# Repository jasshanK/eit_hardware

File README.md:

# WIP 
USE SCHEMATICS AT OWN RISK

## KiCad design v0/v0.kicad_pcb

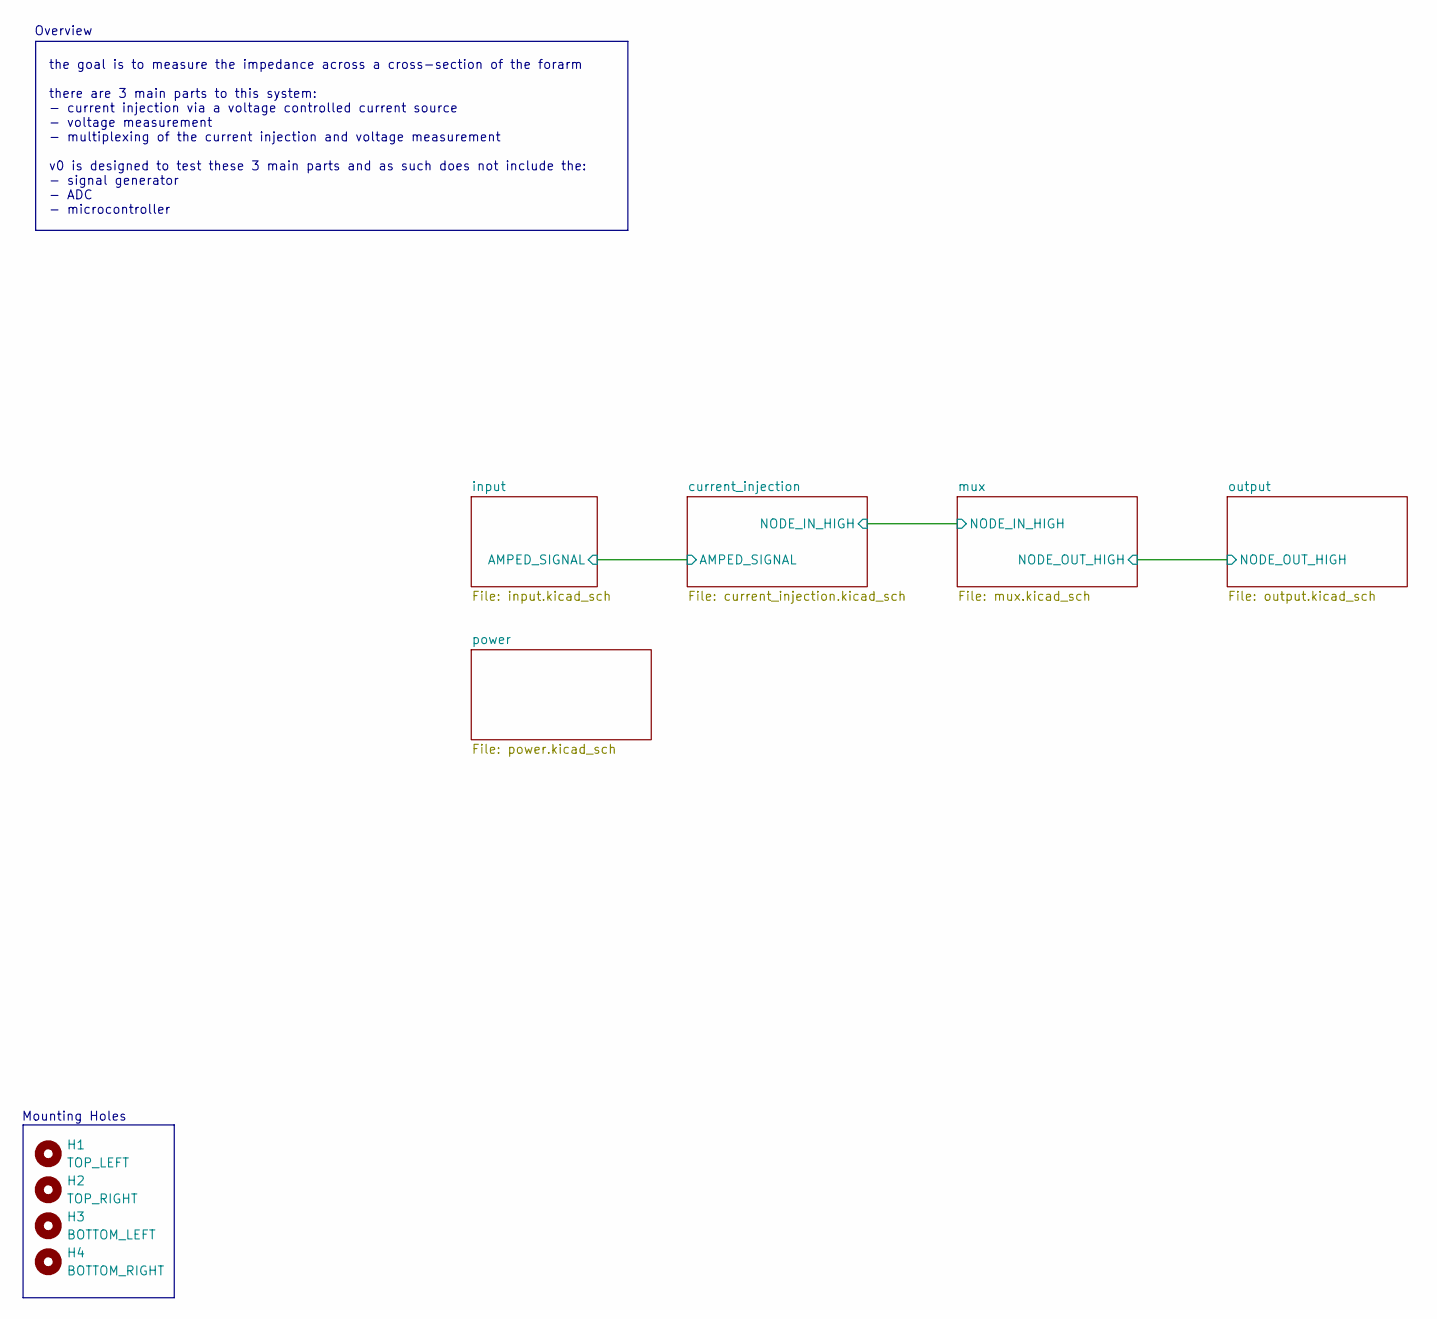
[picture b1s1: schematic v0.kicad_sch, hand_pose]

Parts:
H1: TOP_LEFT; MountingHole_2.2mm_M2
H2: TOP_RIGHT; MountingHole_2.2mm_M2
H3: BOTTOM_LEFT; MountingHole_2.2mm_M2
H4: BOTTOM_RIGHT; MountingHole_2.2mm_M2

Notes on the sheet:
the goal is to measure the impedance across a cross-section of the forarm there are 3 main parts to this system: - current injection via a voltage controlled current source - voltage measurement - multiplexing of the current injection and voltage measurement v0 is designed to test these 3 main part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
Overview
Mounting Holes

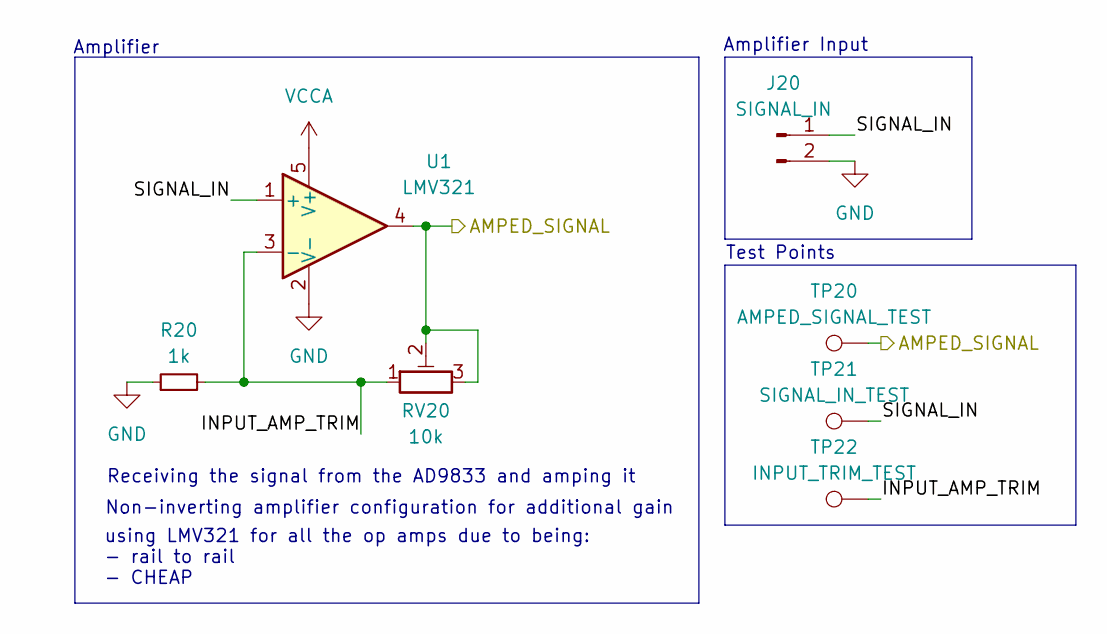
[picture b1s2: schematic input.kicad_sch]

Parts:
J20: SIGNAL_IN; PinHeader_1x02_P2.54mm_Vertical
R20: 1k; R_0402_1005Metric_Pad0.72x0.64mm_HandSolder
RV20: 10k; Potentiometer_Bourns_3296W_Vertical
TP20: AMPED_SIGNAL_TEST; TestPoint_Loop_D1.80mm_Drill1.0mm_Beaded
TP21: SIGNAL_IN_TEST; TestPoint_Loop_D1.80mm_Drill1.0mm_Beaded
TP22: INPUT_TRIM_TEST; TestPoint_Pad_1.0x1.0mm
U1: LMV321; SOT-23-5

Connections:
/current_injection/AMPED_SIGNAL: RV20.2, RV20.3, TP20.1, U1.4; also elsewhere on the board
/input/INPUT_AMP_TRIM: R20.2, RV20.1, TP22.1, U1.3 (-)
/input/SIGNAL_IN: J20.1, TP21.1, U1.1 (+)
GND: J20.2, R20.1, U1.2 (V-); also elsewhere on the board
VCCA: U1.5 (V+); also elsewhere on the board

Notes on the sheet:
Receiving the signal from the AD9833 and amping it
using LMV321 for all the op amps due to being: - rail to rail - CHEAP
Amplifier Input
Test Points
Non-inverting amplifier configuration for additional gain
Amplifier

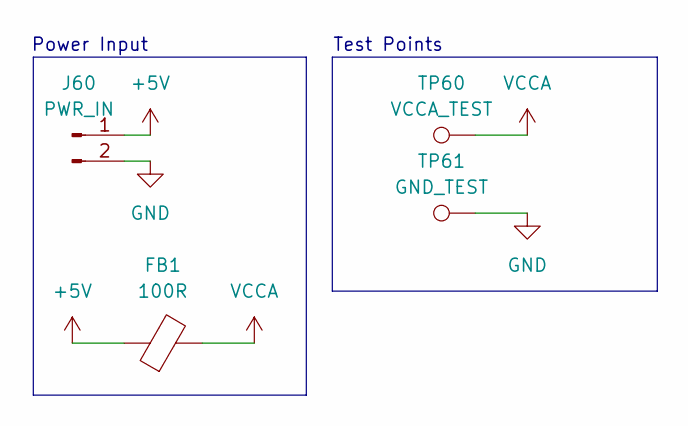
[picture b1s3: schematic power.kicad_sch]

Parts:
FB1: 100R; L_0805_2012Metric_Pad1.05x1.20mm_HandSolder
J60: PWR_IN; PinHeader_1x02_P2.54mm_Vertical
TP60: VCCA_TEST; TestPoint_Loop_D1.80mm_Drill1.0mm_Beaded
TP61: GND_TEST; TestPoint_Loop_D1.80mm_Drill1.0mm_Beaded

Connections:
+5V: FB1.1, J60.1
GND: J60.2, TP61.1; also elsewhere on the board
VCCA: FB1.2, TP60.1; also elsewhere on the board

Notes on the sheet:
Test Points
Power Input

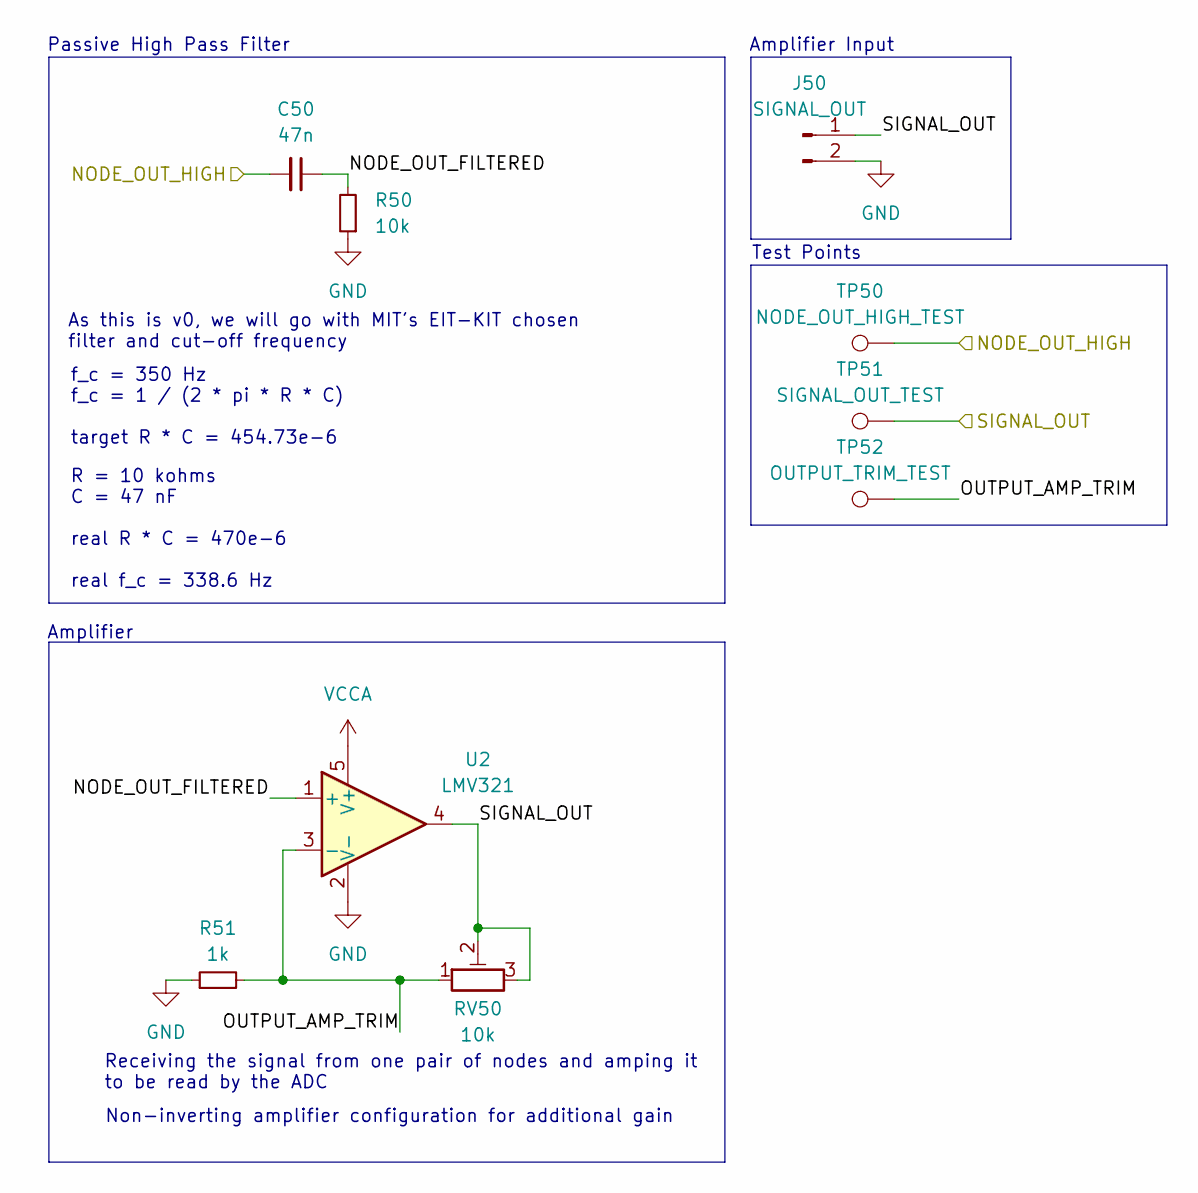
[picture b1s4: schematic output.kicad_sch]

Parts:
C50: 47n; C_0402_1005Metric_Pad0.74x0.62mm_HandSolder
J50: SIGNAL_OUT; PinHeader_1x02_P2.54mm_Vertical
R50: 10k; R_0402_1005Metric_Pad0.72x0.64mm_HandSolder
R51: 1k; R_0402_1005Metric_Pad0.72x0.64mm_HandSolder
RV50: 10k; Potentiometer_Bourns_3296W_Vertical
TP50: NODE_OUT_HIGH_TEST; TestPoint_Loop_D1.80mm_Drill1.0mm_Beaded
TP51: SIGNAL_OUT_TEST; TestPoint_Loop_D1.80mm_Drill1.0mm_Beaded
TP52: OUTPUT_TRIM_TEST; TestPoint_Pad_1.0x1.0mm
U2: LMV321; SOT-23-5

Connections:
/mux/NODE_OUT_HIGH: C50.2, TP50.1; also elsewhere on the board
/output/NODE_OUT_FILTERED: C50.1, R50.2, U2.1 (+)
/output/OUTPUT_AMP_TRIM: R51.2, RV50.1, TP52.1, U2.3 (-)
/output/SIGNAL_OUT: J50.1, RV50.2, RV50.3, TP51.1, U2.4
GND: J50.2, R50.1, R51.1, U2.2 (V-); also elsewhere on the board
VCCA: U2.5 (V+); also elsewhere on the board

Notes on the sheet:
As this is v0, we will go with MIT's EIT-KIT chosen filter and cut-off frequency
f_c = 350 Hz f_c = 1 / (2 * pi * R * C) target R * C = 454.73e-6
Non-inverting amplifier configuration for additional gain
Amplifier
Passive High Pass Filter
Receiving the signal from one pair of nodes and amping it to be read by the ADC
Amplifier Input
Test Points
R = 10 kohms C = 47 nF real R * C = 470e-6 real f_c = 338.6 Hz

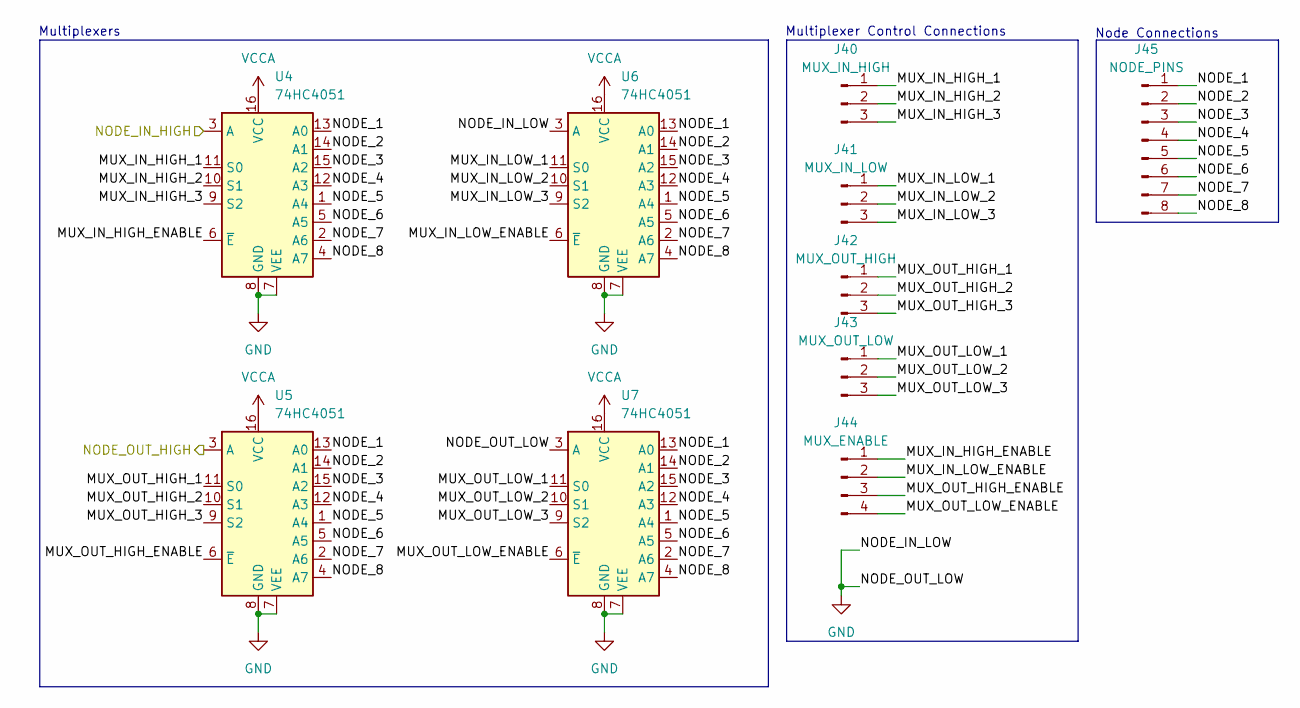
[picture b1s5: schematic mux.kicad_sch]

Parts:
J40: MUX_IN_HIGH; PinHeader_1x03_P2.54mm_Vertical
J41: MUX_IN_LOW; PinHeader_1x03_P2.54mm_Vertical
J42: MUX_OUT_HIGH; PinHeader_1x03_P2.54mm_Vertical
J43: MUX_OUT_LOW; PinHeader_1x03_P2.54mm_Vertical
J44: MUX_ENABLE; PinHeader_1x04_P2.54mm_Vertical
J45: NODE_PINS; PinHeader_2x04_P2.54mm_Vertical
U4, U5, U6, U7: 74HC4051; SOIC-16_3.9x9.9mm_P1.27mm

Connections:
/current_injection/NODE_IN_HIGH: U4.3 (A); also elsewhere on the board
/mux/MUX_IN_HIGH_1: J40.1, U4.11 (S0)
/mux/MUX_IN_HIGH_2: J40.2, U4.10 (S1)
/mux/MUX_IN_HIGH_3: J40.3, U4.9 (S2)
/mux/MUX_IN_HIGH_ENABLE: J44.1, U4.6 (~E)
/mux/MUX_IN_LOW_1: J41.1, U6.11 (S0)
/mux/MUX_IN_LOW_2: J41.2, U6.10 (S1)
/mux/MUX_IN_LOW_3: J41.3, U6.9 (S2)
/mux/MUX_IN_LOW_ENABLE: J44.2, U6.6 (~E)
/mux/MUX_OUT_HIGH_1: J42.1, U5.11 (S0)
/mux/MUX_OUT_HIGH_2: J42.2, U5.10 (S1)
/mux/MUX_OUT_HIGH_3: J42.3, U5.9 (S2)
/mux/MUX_OUT_HIGH_ENABLE: J44.3, U5.6 (~E)
/mux/MUX_OUT_LOW_1: J43.1, U7.11 (S0)
/mux/MUX_OUT_LOW_2: J43.2, U7.10 (S1)
/mux/MUX_OUT_LOW_3: J43.3, U7.9 (S2)
/mux/MUX_OUT_LOW_ENABLE: J44.4, U7.6 (~E)
/mux/NODE_1: J45.1, U4.13 (A0), U5.13 (A0), U6.13 (A0), U7.13 (A0)
/mux/NODE_2: J45.2, U4.14 (A1), U5.14 (A1), U6.14 (A1), U7.14 (A1)
/mux/NODE_3: J45.3, U4.15 (A2), U5.15 (A2), U6.15 (A2), U7.15 (A2)
/mux/NODE_4: J45.4, U4.12 (A3), U5.12 (A3), U6.12 (A3), U7.12 (A3)
/mux/NODE_5: J45.5, U4.1 (A4), U5.1 (A4), U6.1 (A4), U7.1 (A4)
/mux/NODE_6: J45.6, U4.5 (A5), U5.5 (A5), U6.5 (A5), U7.5 (A5)
/mux/NODE_7: J45.7, U4.2 (A6), U5.2 (A6), U6.2 (A6), U7.2 (A6)
/mux/NODE_8: J45.8, U4.4 (A7), U5.4 (A7), U6.4 (A7), U7.4 (A7)
/mux/NODE_OUT_HIGH: U5.3 (A); also elsewhere on the board
GND: U4.7 (VEE), U4.8 (GND), U5.7 (VEE), U5.8 (GND), U6.3 (A), U6.7 (VEE), U6.8 (GND), U7.3 (A), U7.7 (VEE), U7.8 (GND); also elsewhere on the board
VCCA: U4.16 (VCC), U5.16 (VCC), U6.16 (VCC), U7.16 (VCC); also elsewhere on the board

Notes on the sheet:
Multiplexer Control Connections
Multiplexers
Node Connections

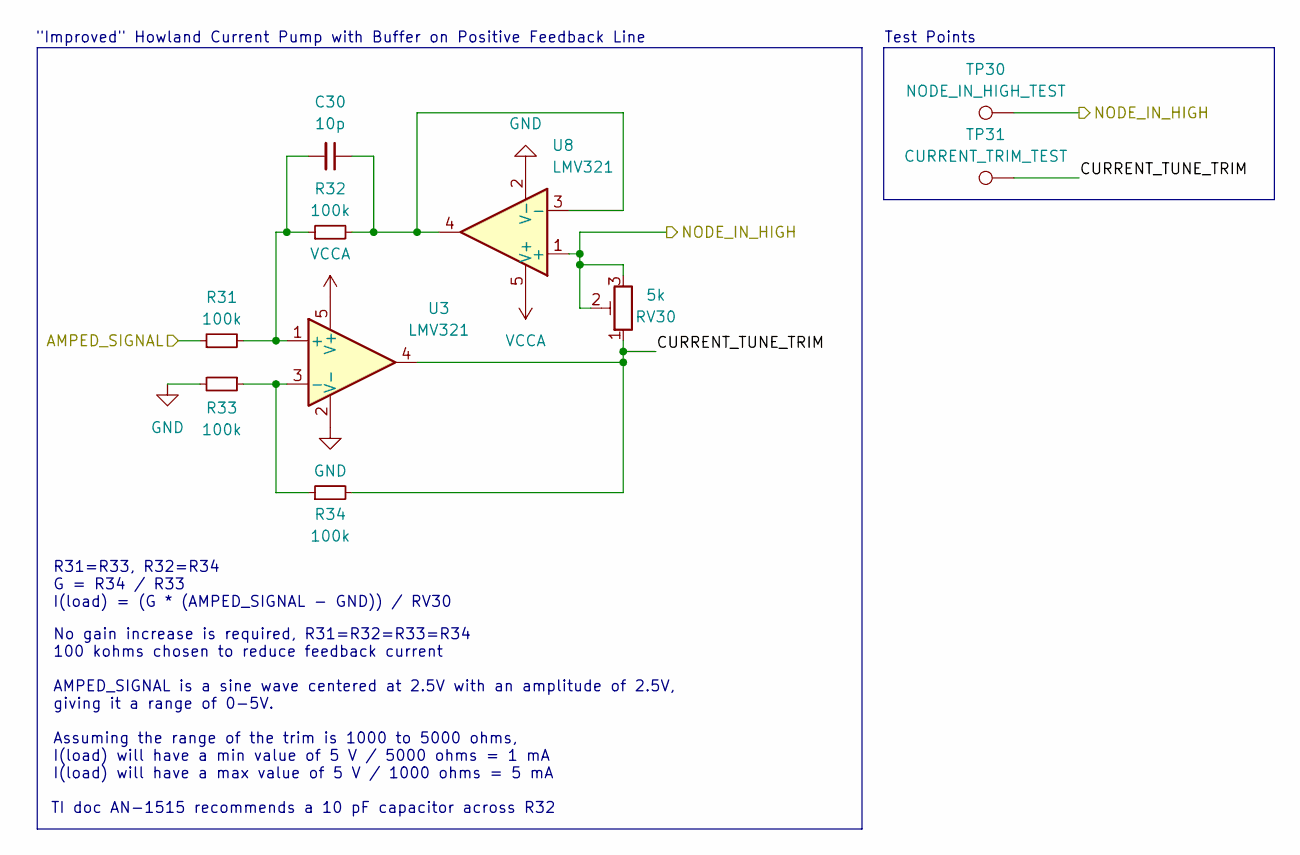
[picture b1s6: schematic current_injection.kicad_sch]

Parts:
C30: 10p; C_0402_1005Metric_Pad0.74x0.62mm_HandSolder
R31, R32, R33, R34: 100k; R_0805_2012Metric_Pad1.20x1.40mm_HandSolder
RV30: 5k; Potentiometer_Bourns_3296W_Vertical
TP30: NODE_IN_HIGH_TEST; TestPoint_Loop_D1.80mm_Drill1.0mm_Beaded
TP31: CURRENT_TRIM_TEST; TestPoint_Pad_1.0x1.0mm
U3, U8: LMV321; SOT-23-5

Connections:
/current_injection/AMPED_SIGNAL: R31.1; also elsewhere on the board
/current_injection/CURRENT_TUNE_TRIM: R34.2, RV30.1, TP31.1, U3.4
/current_injection/NODE_IN_HIGH: RV30.2, RV30.3, TP30.1, U8.1 (+); also elsewhere on the board
GND: R33.2, U3.2 (V-), U8.2 (V-); also elsewhere on the board
unnamed: C30.2, R31.2, R32.1, U3.1 (+)
unnamed: R33.1, R34.1, U3.3 (-)
unnamed: C30.1, R32.2, U8.3 (-), U8.4
VCCA: U3.5 (V+), U8.5 (V+); also elsewhere on the board

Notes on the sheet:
Test Points
Assuming the range of the trim is 1000 to 5000 ohms, I(load) will have a min value of 5 V / 5000 ohms = 1 mA I(load) will have a max value of 5 V / 1000 ohms = 5 mA
"Improved" Howland Current Pump with Buffer on Positive Feedback Line
TI doc AN-1515 recommends a 10 pF capacitor across R32
No gain increase is required, R31=R32=R33=R34 100 kohms chosen to reduce feedback current
R31=R33, R32=R34 G = R34 / R33 I(load) = (G * (AMPED_SIGNAL - GND)) / RV30
AMPED_SIGNAL is a sine wave centered at 2.5V with an amplitude of 2.5V, giving it a range of 0-5V.

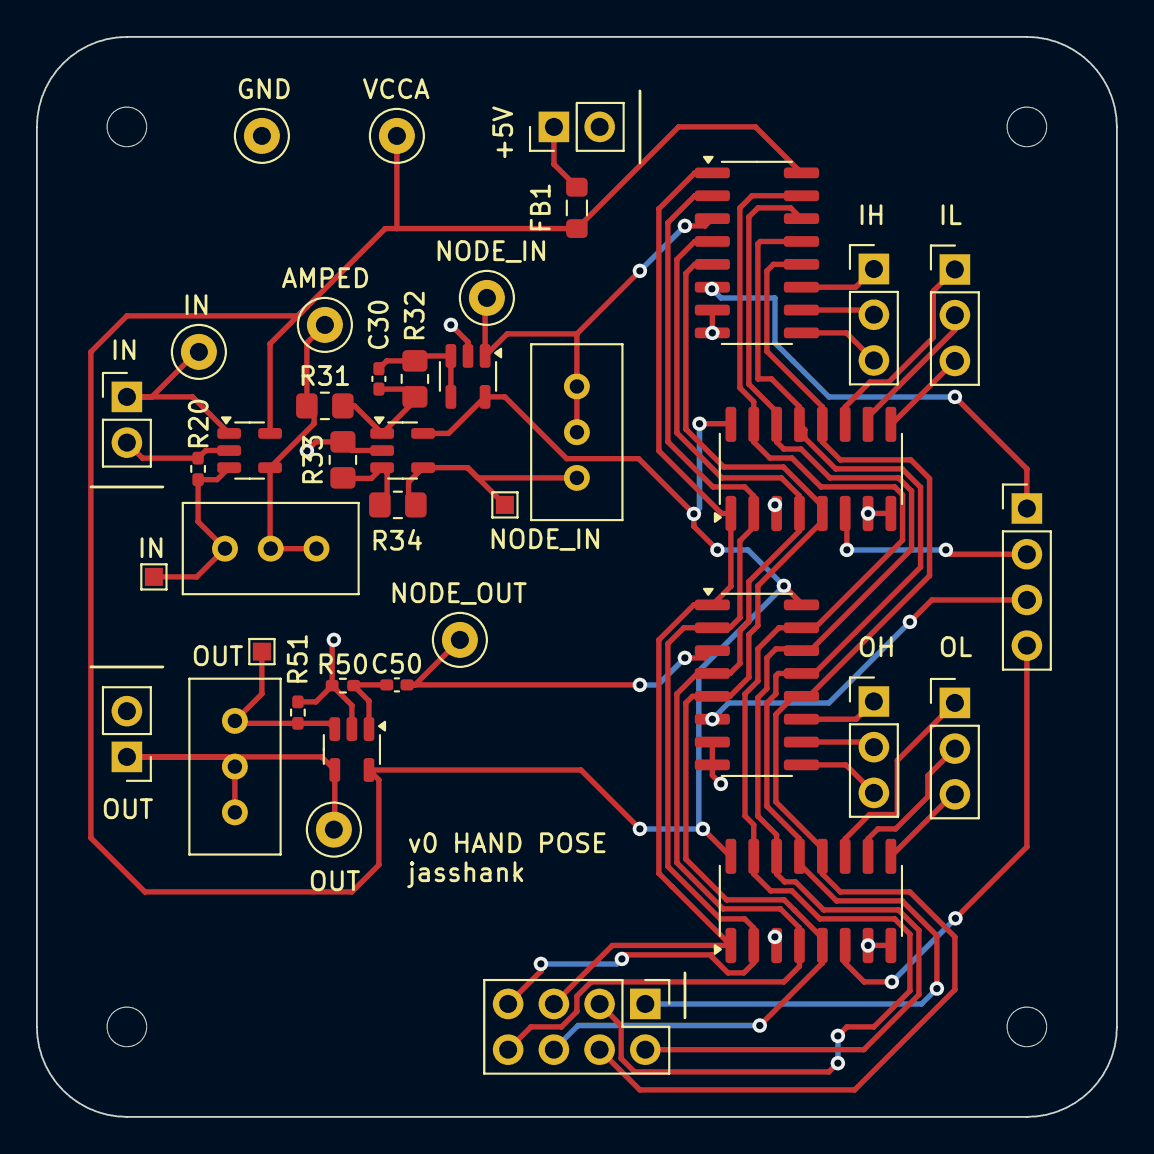
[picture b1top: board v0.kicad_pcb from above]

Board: 2 copper layers, 60.0 x 60.0 mm, 44 parts (0 on the bottom side), 39 nets.

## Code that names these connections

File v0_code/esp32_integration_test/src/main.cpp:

#include <Arduino.h>
#include <MD_AD9833.h>
#include <Adafruit_ADS1X15.h>

// need a LOT of pins for the MUX
// should get a gpio extender or a board with more pins

// pinout 
// https://docs.espressif.com/projects/esp-dev-kits/en/latest/esp32s3/_images/ESP32-S3_DevKitC-1_pinlayout_v1.1.jpg

#define MUX_IN_HIGH_ENABLE 4
#define MUX_IN_LOW_ENABLE 5
#define MUX_OUT_HIGH_ENABLE 6
#define MUX_OUT_LOW_ENABLE 7
#define MUX_IN_HIGH_1 1
#define MUX_IN_HIGH_2 2
#define MUX_IN_HIGH_3 42
#define MUX_IN_LOW_1 41
#define MUX_IN_LOW_2 40
#define MUX_IN_LOW_3 39
#define MUX_OUT_HIGH_1 38
#define MUX_OUT_HIGH_2 37
#define MUX_OUT_HIGH_3 36
#define MUX_OUT_LOW_1 48
#define MUX_OUT_LOW_2 47
#define MUX_OUT_LOW_3 21



#define SPI_DATA_PIN 13 
#define SPI_CLK_PIN 12
#define SPI_CS_PIN 10
MD_AD9833 AD(SPI_DATA_PIN, SPI_CLK_PIN, SPI_CS_PIN);

#define I2C_SDA 11
#define I2C_SCL 14
TwoWire i2c_wire(0);

#define ADC_ADDR 0x48
Adafruit_ADS1115 ads;

enum MUX_TYPE {
  MUX_IN_HIGH,
  MUX_IN_LOW,
  MUX_OUT_HIGH,
  MUX_OUT_LOW
};

#define FIRST_PIN 1
#define LAST_PIN 8
int setMux(int mux_type, int target_pin);

void setup() {
  Serial.begin(9600);

  assert(i2c_wire.begin(I2C_SDA, I2C_SCL));
  assert(ads.begin(ADC_ADDR, &i2c_wire));

  ads.setDataRate(400);
  AD.begin();
  AD.setMode(MD_AD9833::MODE_SINE);
  AD.setFrequency(MD_AD9833::CHAN_0, 50000.0);

  pinMode(MUX_IN_HIGH_ENABLE, OUTPUT); pinMode(MUX_IN_LOW_ENABLE, OUTPUT);
  pinMode(MUX_OUT_HIGH_ENABLE, OUTPUT);
  pinMode(MUX_OUT_LOW_ENABLE, OUTPUT);

  pinMode(MUX_IN_HIGH_1, OUTPUT);
  pinMode(MUX_IN_HIGH_2, OUTPUT);
  pinMode(MUX_IN_HIGH_3, OUTPUT);
  pinMode(MUX_IN_LOW_1, OUTPUT);
  pinMode(MUX_IN_LOW_2, OUTPUT);
  pinMode(MUX_IN_LOW_3, OUTPUT);

  pinMode(MUX_OUT_HIGH_1, OUTPUT);
  pinMode(MUX_OUT_HIGH_2, OUTPUT);
  pinMode(MUX_OUT_HIGH_3, OUTPUT);
  pinMode(MUX_OUT_LOW_1, OUTPUT);
  pinMode(MUX_OUT_LOW_2, OUTPUT);
  pinMode(MUX_OUT_LOW_3, OUTPUT);

  // active low enable
  digitalWrite(MUX_IN_HIGH_ENABLE, HIGH);
  digitalWrite(MUX_IN_LOW_ENABLE, HIGH);
  digitalWrite(MUX_OUT_HIGH_ENABLE, HIGH);
  digitalWrite(MUX_OUT_LOW_ENABLE, HIGH);

  digitalWrite(MUX_IN_HIGH_1, LOW);
  digitalWrite(MUX_IN_HIGH_2, LOW);
  digitalWrite(MUX_IN_HIGH_3, LOW);
  digitalWrite(MUX_IN_LOW_1, LOW);
  digitalWrite(MUX_IN_LOW_2, LOW);
  digitalWrite(MUX_IN_LOW_3, LOW);

  digitalWrite(MUX_OUT_HIGH_1, LOW);
  digitalWrite(MUX_OUT_HIGH_2, LOW);
  digitalWrite(MUX_OUT_HIGH_3, LOW);
  digitalWrite(MUX_OUT_LOW_1, LOW);
  digitalWrite(MUX_OUT_LOW_2, LOW);
  digitalWrite(MUX_OUT_LOW_3, LOW);

}

void loop() {
  int16_t adc0 = 0;
  float volts0 = 0.0;
  for (int i = 0; i < 8; i++) {
    int node_in_high = ((0 + i) % 8) + 1;
    int node_in_low = ((1 + i) % 8) + 1;
    //Serial.printf("%d %d\n", node_in_high, node_in_low);

    setMux(MUX_IN_HIGH, node_in_high);
    setMux(MUX_IN_LOW, node_in_low);
    for (int j = 0; j < 5; j++) {
      int node_out_high = (node_in_high - 1 + 2 + j) % 8 + 1;
      int node_out_low = (node_in_low - 1 + 2 + j) % 8 + 1;
      // Serial.printf("%d %d,", node_out_high, node_out_low);

      setMux(MUX_OUT_HIGH, node_out_high);
      setMux(MUX_OUT_LOW, node_out_low);
      delay(10);

      adc0 = ads.readADC_SingleEnded(0);
      volts0 = ads.computeVolts(adc0);

      Serial.printf("/*%f*/\n", volts0);
    }
    Serial.printf("\n");
  }

  Serial.printf("\n\n");
  delay(1000);
}

int setMux(int mux_type, int target_pin) 
{
  if (target_pin < FIRST_PIN || target_pin > LAST_PIN) {
    return EXIT_FAILURE;
  }

  if (mux_type == MUX_IN_HIGH) {
    digitalWrite(MUX_IN_HIGH_ENABLE, HIGH);
    digitalWrite(MUX_IN_HIGH_1, ((target_pin - 1) >> 0) & 0b01);
    digitalWrite(MUX_IN_HIGH_2, ((target_pin - 1) >> 1) & 0b01);
    digitalWrite(MUX_IN_HIGH_3, ((target_pin - 1) >> 2) & 0b01);
    digitalWrite(MUX_IN_HIGH_ENABLE, LOW);
  } else if (mux_type == MUX_IN_LOW) {
    digitalWrite(MUX_IN_LOW_ENABLE, HIGH);
    digitalWrite(MUX_IN_LOW_1, ((target_pin - 1) >> 0) & 0b01);
    digitalWrite(MUX_IN_LOW_2, ((target_pin - 1) >> 1) & 0b01);
    digitalWrite(MUX_IN_LOW_3, ((target_pin - 1) >> 2) & 0b01);
    digitalWrite(MUX_IN_LOW_ENABLE, LOW);
  } else if (mux_type == MUX_OUT_HIGH) {
    digitalWrite(MUX_OUT_HIGH_ENABLE, HIGH);
    digitalWrite(MUX_OUT_HIGH_1, ((target_pin - 1) >> 0) & 0b01);
    digitalWrite(MUX_OUT_HIGH_2, ((target_pin - 1) >> 1) & 0b01);
    digitalWrite(MUX_OUT_HIGH_3, ((target_pin - 1) >> 2) & 0b01);
    digitalWrite(MUX_OUT_HIGH_ENABLE, LOW);
  } else if (mux_type == MUX_OUT_LOW) {
    digitalWrite(MUX_OUT_LOW_ENABLE, HIGH);
    digitalWrite(MUX_OUT_LOW_1, ((target_pin - 1) >> 0) & 0b01);
    digitalWrite(MUX_OUT_LOW_2, ((target_pin - 1) >> 1) & 0b01);
    digitalWrite(MUX_OUT_LOW_3, ((target_pin - 1) >> 2) & 0b01);
    digitalWrite(MUX_OUT_LOW_ENABLE, LOW);
  } else {
    return EXIT_FAILURE;
  }

  return EXIT_SUCCESS;
}

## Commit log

2025-01-02 finally putting it on git
2025-02-14 esp32-based integration test of the board
